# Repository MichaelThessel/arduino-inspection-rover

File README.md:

# Camera inspection rover

This repository contains the firmware and the CAD files used to construct a
basic camera inspection rover.

# Components

The rover is build based on a modified 1:18 scale RC car.
The model used here is a PulseLabZ HS18321 but this should work with pretty much
any RC car.

The car is modified to work with a Futaba R2004GF 2.4GHz 4 channel receiver.

2 Channels of the receiver control the servos for the X and Y axis of the camera
gimbal. One channel controls the motor speed and the remaining channel controls
the servo for the steering.

The 2 servos in the gimbal are Hobby King HK-933MG.

For the motor speed controller I opted for the Hobbywing Quicrun 1060 60A 2S-3S
ESC (brushed).

# Gimbal

The gimbal is a custom design meant for a GoPro 7. It uses 2 standard RC servos.

The cad files for the gimbal are in the [cad/gimbal](cad/gimbal) directory.

The gimbal also has a light bar attached. The light bar is a simple custom
etched PCB with 0805 LEDs (white) and 0805 resistors (220R).

The design files for the light bar are in the [pcb/light-bar](pcb/light-bar)
directory.

The STL files for the gimbal are also available on
[Thingiverse](https://www.thingiverse.com/thing:4635363).

# Motor control

One of the challenges was that the RC car was meant to go fast.  For the
intended use case a slow speed was desired though. Simply being careful with the
control sticks wasn't really working as the slightest input resulted in
significant acceleration.

I used an Arduino Pro Mini to sample the PWM signal from the RC receiver and
then mapped it into a new PWM signal that would drive the motor at a reduced
speed. This also accounts for the fact that the car normally drives faster when
going forward than going backward when given the same input. With the custom
firmware the forward and reverse speed is the same.

The firmware for the motor control is in the [src/firmware](src/firmware)
directory.

# Steering

Another issue was that the servo to control the steering was a 5 wire servo and
not a conventional 3 wire servo. To make the steering servo compatible with the
RC receiver I transplanted the electronics from a standard 3 wire servo into
the 5 wire servo.

The process for that is quite straight forward. There is a good video available
[here](https://www.youtube.com/watch?v=GDukjyycyxo).

# Enclosures

The rover uses 2 enclosures. One for the battery and one for the rest of the
electronics. The reason to separate this is to prevent having to access the
electronics compartment when switching out the battery.

The cad files for the enclosures are in the [cad/box](cad/box) directory.

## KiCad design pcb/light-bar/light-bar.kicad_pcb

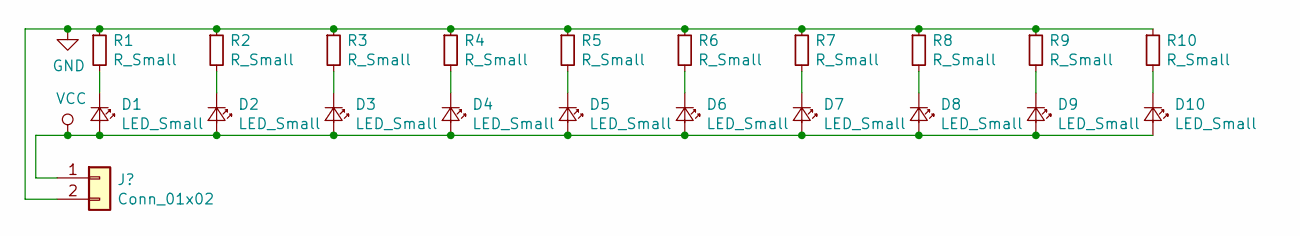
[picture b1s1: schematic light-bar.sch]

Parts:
D1, D2, D3, D4, D5, D6, D7, D8, D9, D10: LED_Small; LED_0805_2012Metric
R1, R2, R3, R4, R5, R6, R7, R8, R9, R10: R_Small; R_0805_2012Metric

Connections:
GND: R1.1, R2.1, R3.1, R4.1, R5.1, R6.1, R7.1, R8.1, R9.1, R10.1; also elsewhere on the board
unnamed: D1.1 (K), R1.2
unnamed: D2.1 (K), R2.2
unnamed: D3.1 (K), R3.2
unnamed: D4.1 (K), R4.2
unnamed: D5.1 (K), R5.2
unnamed: D6.1 (K), R6.2
unnamed: D7.1 (K), R7.2
unnamed: D8.1 (K), R8.2
unnamed: D9.1 (K), R9.2
unnamed: D10.1 (K), R10.2
VCC: D1.2 (A), D2.2 (A), D3.2 (A), D4.2 (A), D5.2 (A), D6.2 (A), D7.2 (A), D8.2 (A), D9.2 (A), D10.2 (A); also elsewhere on the board

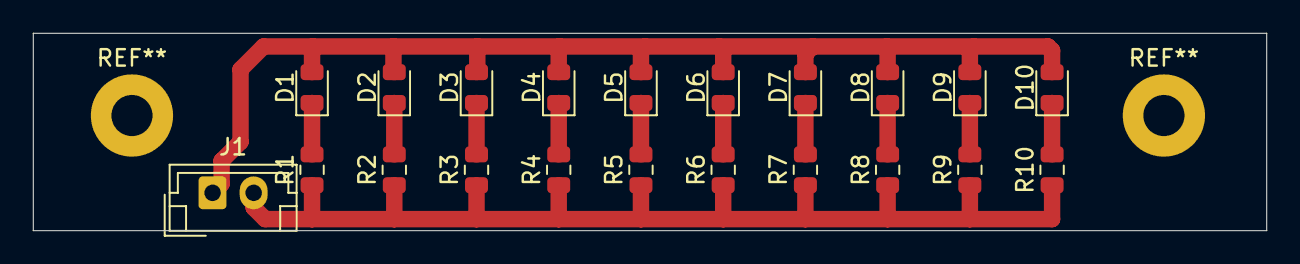
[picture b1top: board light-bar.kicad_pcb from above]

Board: 2 copper layers, 75.0 x 12.0 mm, 21 parts (0 on the bottom side), 12 nets.

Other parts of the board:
J1: Conn_01x02; JST_EH_B2B-EH-A_1x02_P2.50mm_Vertical

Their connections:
GND: J1.2; also elsewhere on the board
VCC: J1.1; also elsewhere on the board

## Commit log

2020-09-09 Added camera control
2020-09-10 Renamed project
2020-09-10 Re-structured project
2020-09-14 Added PWM signal generation
2020-09-14 Moved class constants into class header
2020-09-15 Made file names lowercase
2020-09-15 Removed uneccessary extern
2020-09-15 Removed unnecessary qualifier
2020-09-15 Added reset sequence
2020-09-15 Added readme
2020-09-18 Added gimbal CAD files
2020-09-19 Added camera mount
2020-09-19 Added camera mount back cutout
2020-09-20 Added difference fix
2020-09-20 Positioned gimbal components
2020-09-20 Added frame
2020-09-21 Reduced support dimensions
2020-09-23 Only use timer 1 to control x and y axis
2020-10-02 Added frame servo cutout and mounting pin
2020-10-02 Refined camera mount
2020-10-06 Added screw holes
2020-10-06 Renamed variable
2020-10-06 Added cutout for camera shutter to frame
2020-10-06 Changed camera mount offset
2020-10-06 Improved support design
2020-10-06 Added servo cutout
2020-10-06 Set correct frame height
2020-10-06 Corrected camera mount position
2020-10-06 Added frame printing templates
2020-10-06 Added mounting points for LED strip
2020-10-06 Added screw hole for lock
2020-10-06 Added lock for camera
2020-10-09 Added lightbar PCB
2020-10-09 Moved src files
2020-10-09 Moved light bar pcb files
2020-10-09 Moved mounting holes
2020-10-14 Added frame extensions to account for GoPro fisheye lens
2020-10-19 Added designs for battery and electronics compartment
2020-10-19 Increased screw hole radius
2020-10-21 Added gimbal image
2020-10-21 Updated gimbal image
2020-10-23 Moved firmware
2020-10-24 Added gimbal blender file
2020-10-24 Removed camera controls
2020-10-24 Added motor speed control
2020-10-24 Added rover images
2020-10-24 Reduced PWM generate to one timer
2020-10-26 Use 16-Bit timer for motor control
2020-10-26 Resized images
2020-10-26 Create LICENSE
2020-10-26 Fixed typo
2020-10-27 Added thingiverse link
